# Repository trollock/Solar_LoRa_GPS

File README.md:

# Solar_LoRa_GPS
files related to the development of the Solar LoRa GPS radiotransceiver including information on the hardware and software

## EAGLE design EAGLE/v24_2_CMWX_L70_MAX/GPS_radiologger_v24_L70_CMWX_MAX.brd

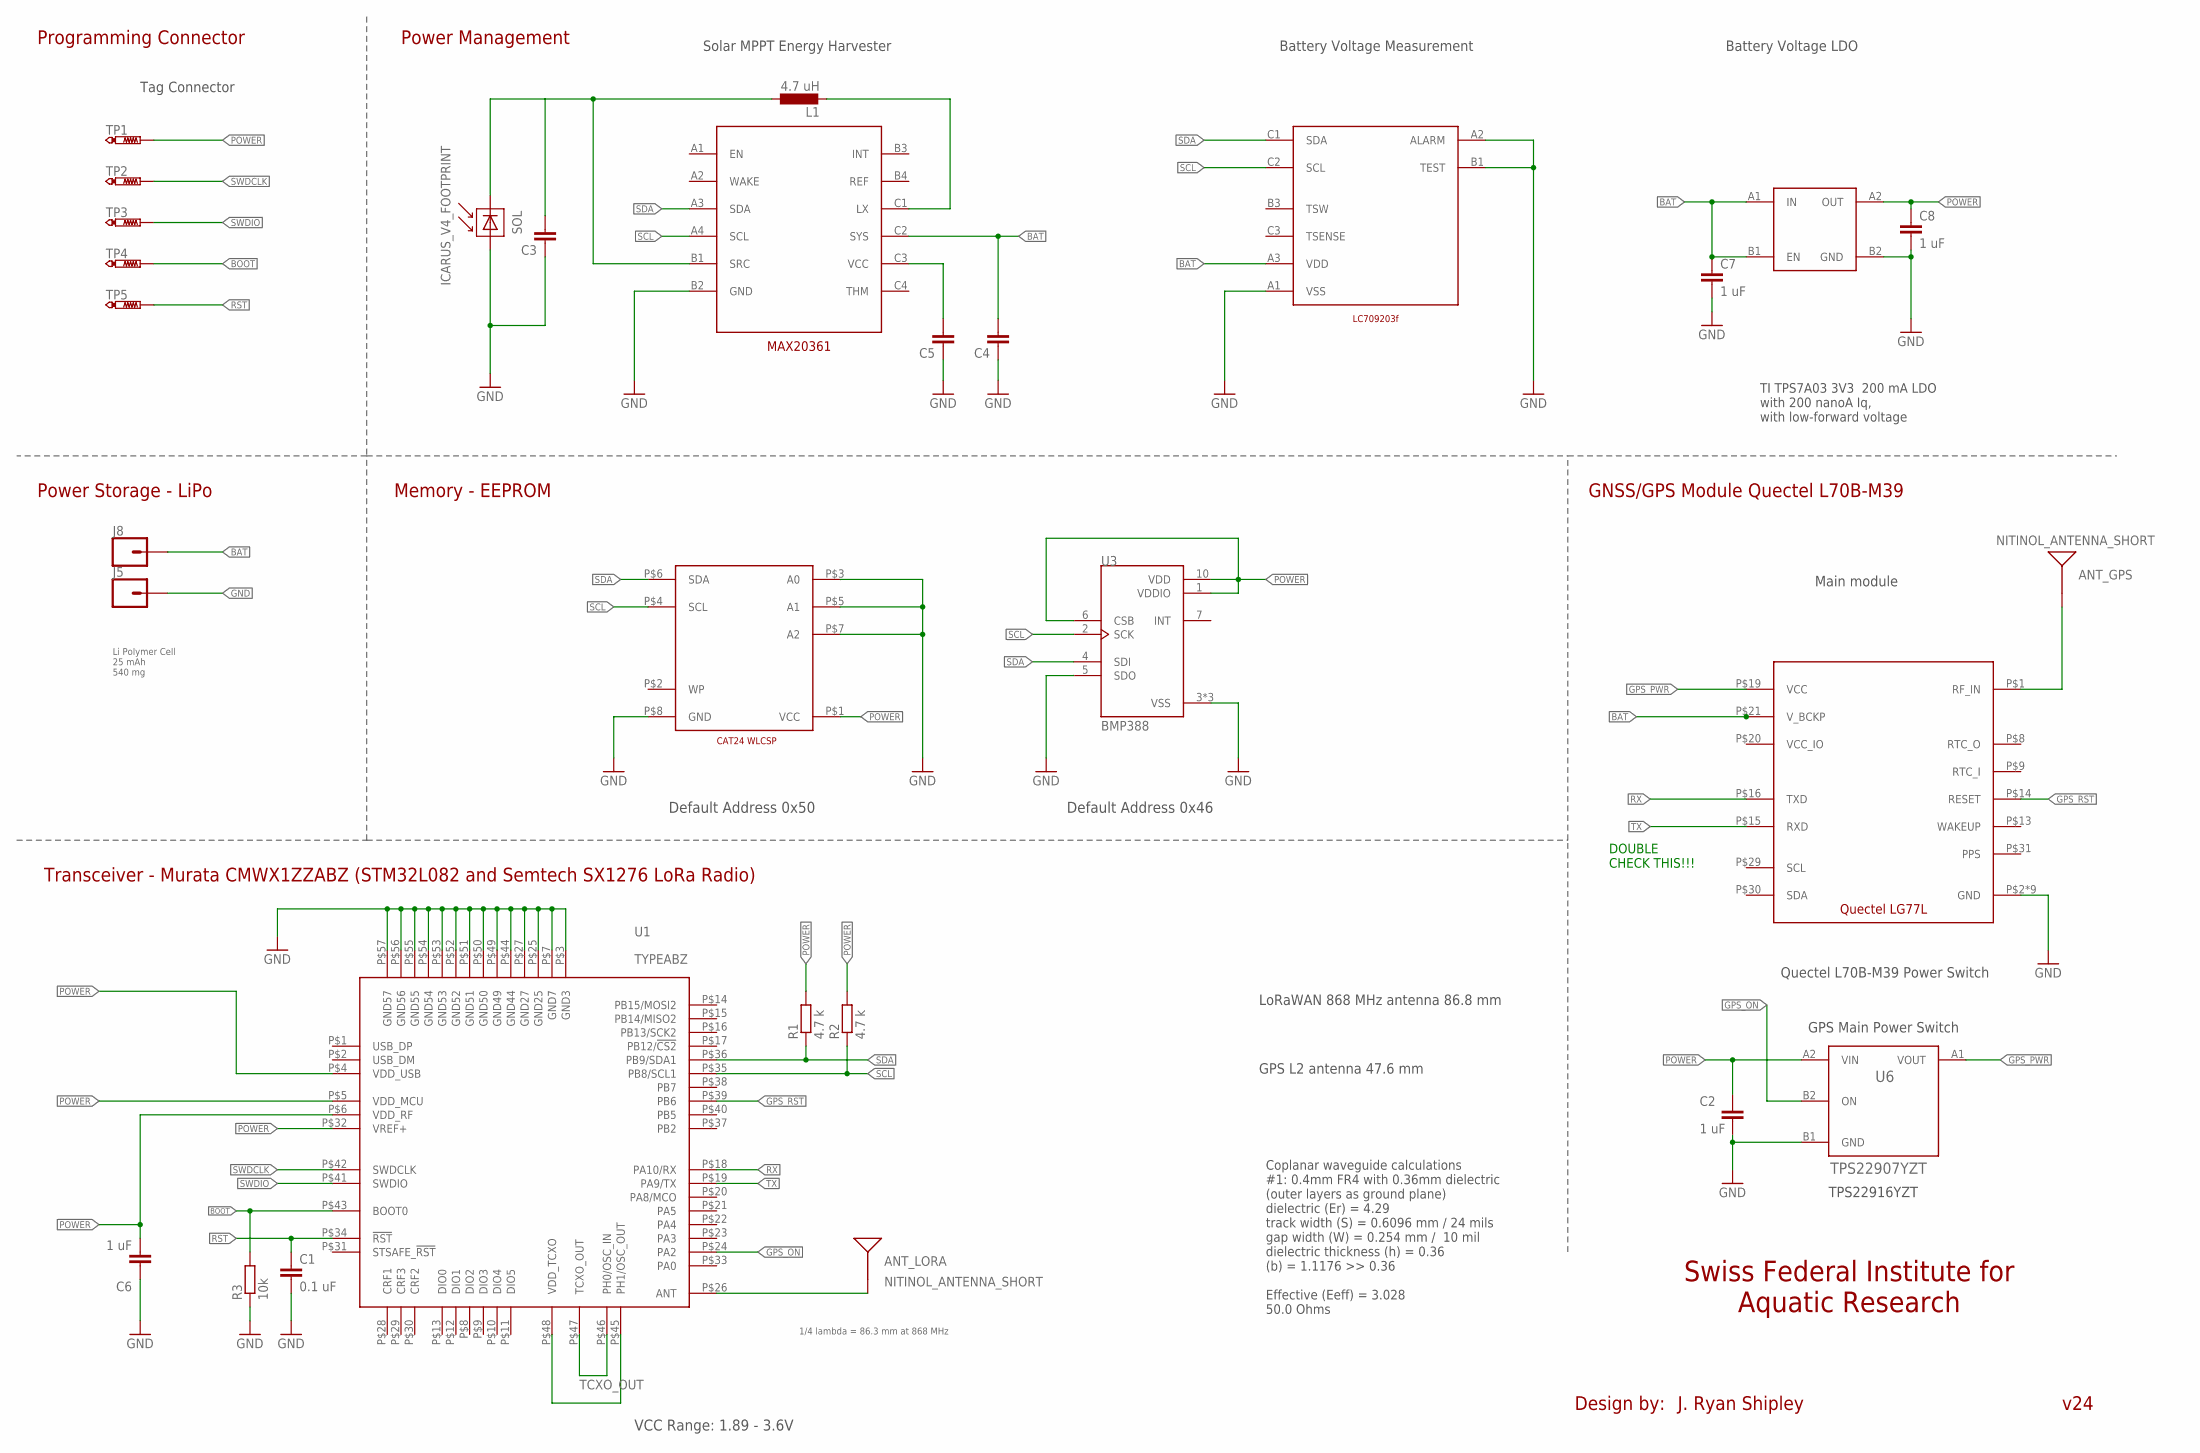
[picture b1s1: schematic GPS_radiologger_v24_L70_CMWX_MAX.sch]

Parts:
ANT_GPS: NITINOL_ANTENNA_SHORT; ICARUS_NITINOL_ANTENNA_SHORT
ANT_LORA: NITINOL_ANTENNA_SHORT; ICARUS_NITINOL_ANTENNA_SHORT
C1: 0.1 uF; C0201
C2, C6: 1 uF; C0201
C3: 10UF; 0603-TIGHT
C4, C5: 1.0UF; 0402-TIGHTER
C7, C8: 1 uF; 0402-CAP
J5, J8: CONN_01PTH_NO_SILK_SMALL; 1X01_SMALL
L1: 4.7 uH; INDC2016X120L
R1, R2: 4.7 k; R0201
R3: 10k; R0201
SOL: ICARUS_V4_FOOTPRINT; ICARUS_FULL_FOOTPRINT
TP1, TP2, TP3, TP4, TP5: PTR1TP08SQ; TP08SQ
U1: TYPEABZ
U3: BMP388; PQFN50P200X200X80-10N
U4: TPS7A03-DSBGA; BGA4N35P2X2_70X70X40N
U5: LC709203F; BGA9N50P3X3_160X175X50N
U6: TPS22907YZT; YFP0004-DSBGA
U7: CAT24_WLCSP8; WLCSP8
U8: MAX20361; BGA12N40P4X3_123X163X64N
U$1: LG77L

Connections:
BAT: C4.P$2 (2), C7.1, J8.P$1, U4.A1 (IN), U4.B1 (EN), U5.A3 (VDD), U8.C2 (SYS), U$1.P$21 (V_BCKP)
BOOT: R3.2, TP4.TP, U1.P$43 (BOOT0)
GND: C1.2, C2.2, C3.P$1 (1), C4.P$1 (1), C5.P$1 (1), C6.1, C7.2, C8.2, J5.P$1, R3.1, SOL.P$2 (MINUS), U1.P$3 (GND3), U1.P$7 (GND7), U1.P$25 (GND25), U1.P$27 (GND27), U1.P$44 (GND44), U1.P$49 (GND49), U1.P$50 (GND50), U1.P$51 (GND51), U1.P$52 (GND52), U1.P$53 (GND53), U1.P$54 (GND54), U1.P$55 (GND55), U1.P$56 (GND56), U1.P$57 (GND57), U3.3 (VSS), U3.5 (SDO), U3.8 (VSS), U3.9 (VSS), U4.B2 (GND), U5.A1 (VSS), U5.A2 (ALARM), U5.B1 (TEST), U6.B1 (GND), U7.P$3 (A0), U7.P$5 (A1), U7.P$7 (A2), U7.P$8 (GND), U8.B2 (GND), U$1.P$2 (GND), U$1.P$18 (GND), U$1.P$37 (GND), U$1.P$38 (GND), U$1.P$39 (GND), U$1.P$40 (GND), U$1.P$41 (GND), U$1.P$42 (GND), U$1.P$43 (GND)
GPS_ON: U1.P$24 (PA2), U6.B2 (ON)
GPS_PWR: U6.A1 (VOUT), U$1.P$19 (VCC)
GPS_RST: U1.P$39 (PB6), U$1.P$14 (RESET)
unnamed: U1.P$45 (PH1/OSC_OUT), U1.P$48 (VDD_TCXO)
unnamed: ANT_GPS.1, ANT_GPS.2, ANT_GPS.3, U$1.P$1 (RF_IN)
unnamed: L1.2, U8.C1 (LX)
unnamed: C5.P$2 (2), U8.C3 (VCC)
unnamed: ANT_LORA.1, ANT_LORA.2, ANT_LORA.3, U1.P$26 (ANT)
unnamed: C3.P$2 (2), L1.1, SOL.P$1 (PLUS), U8.B1 (SRC)
POWER: C2.1, C6.2, C8.1, R1.2, R2.2, TP1.TP, U1.P$4 (VDD_USB), U1.P$5 (VDD_MCU), U1.P$6 (VDD_RF), U1.P$32 (VREF+), U3.1 (VDDIO), U3.6 (CSB), U3.10 (VDD), U4.A2 (OUT), U6.A2 (VIN), U7.P$1 (VCC)
RST: C1.1, TP5.TP, U1.P$34 (!RST)
RX: U1.P$18 (PA10/RX), U$1.P$16 (TXD)
SCL: R2.1, U1.P$35 (PB8/SCL1), U3.2 (SCK), U5.C2 (SCL), U7.P$4 (SCL), U8.A4 (SCL)
SDA: R1.1, U1.P$36 (PB9/SDA1), U3.4 (SDI), U5.C1 (SDA), U7.P$6 (SDA), U8.A3 (SDA)
SWDCLK: TP2.TP, U1.P$42 (SWDCLK)
SWDIO: TP3.TP, U1.P$41 (SWDIO)
TCXO_OUT: U1.P$46 (PH0/OSC_IN), U1.P$47 (TCXO_OUT)
TX: U1.P$19 (PA9/TX), U$1.P$15 (RXD)

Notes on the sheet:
GNSS/GPS Module Quectel L70B-M39
VCC Range: 1.89 - 3.6V
Swiss Federal Institute for Aquatic Research
Transceiver - Murata CMWX1ZZABZ (STM32L082 and Semtech SX1276 LoRa Radio)
Programming Connector
Power Storage - LiPo
Design by:
J. Ryan Shipley
v24
Li Polymer Cell 25 mAh 540 mg
Power Management
Solar MPPT Energy Harvester
Memory - EEPROM
Main module
Coplanar waveguide calculations #1: 0.4mm FR4 with 0.36mm dielectric (outer layers as ground plane) dielectric (Er) = 4.29 track width (S) = 0.6096 mm / 24 mils gap width (W) = 0.254 mm / 10 mil dielectric thickness (h) = 0.36 (b) = 1.1176 >> 0.36 Effective (Eeff) = 3.028 50.0 Ohms
Tag Connector
Default Address 0x50
1/4 lambda = 86.3 mm at 868 MHz
GPS Main Power Switch
TI TPS7A03 3V3 200 mA LDO with 200 nanoA Iq, with low-forward voltage
Quectel L70B-M39 Power Switch
Battery Voltage Measurement
Battery Voltage LDO
Default Address 0x46
TPS22916YZT
GPS L2 antenna 47.6 mm
LoRaWAN 868 MHz antenna 86.8 mm
DOUBLE CHECK THIS!!!

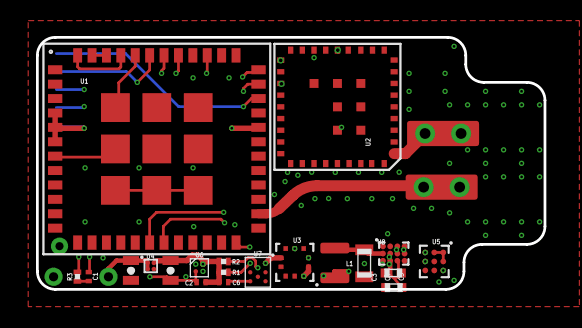
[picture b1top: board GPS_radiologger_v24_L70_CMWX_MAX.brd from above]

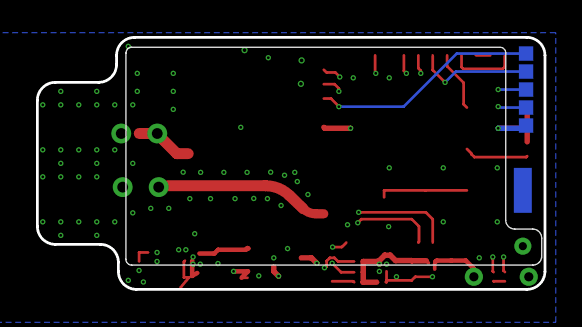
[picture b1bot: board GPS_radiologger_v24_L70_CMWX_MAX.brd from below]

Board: 4 copper layers, 28.2 x 14.0 mm, 30 parts (7 on the bottom side), 21 nets.

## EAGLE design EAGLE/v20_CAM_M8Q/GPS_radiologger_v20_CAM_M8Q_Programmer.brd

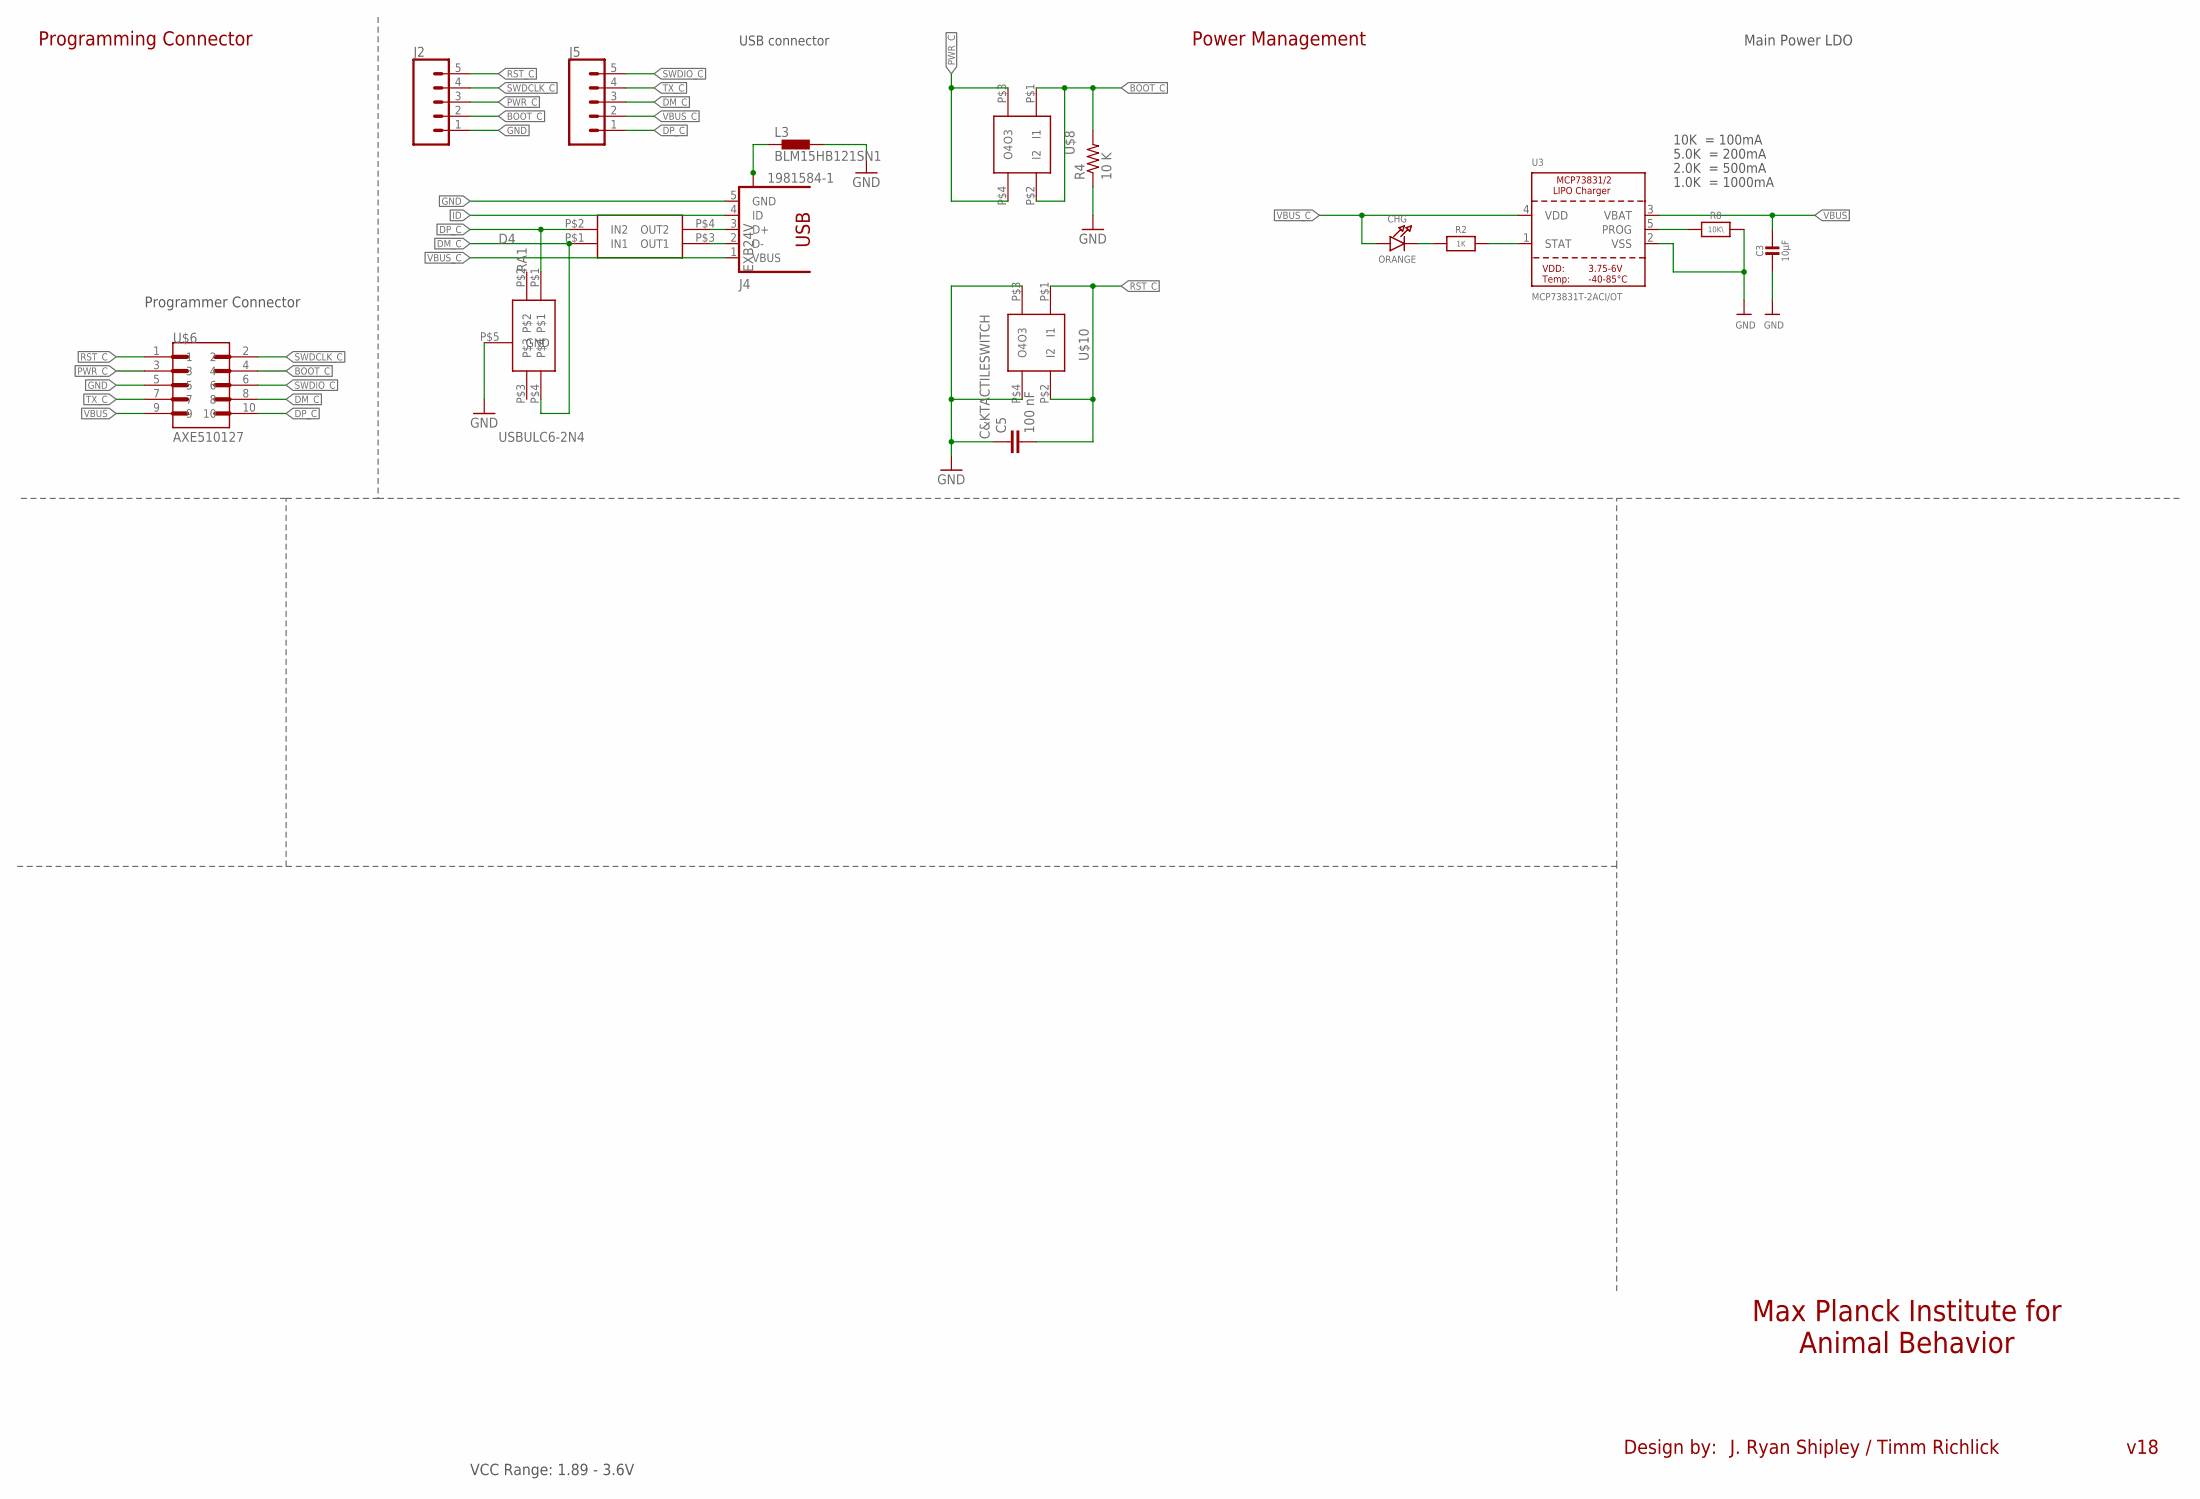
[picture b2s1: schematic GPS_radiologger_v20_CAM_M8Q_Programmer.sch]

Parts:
C3: 10µF; 0805-NO
C5: 100 nF; 0402-CAP
CHG: ORANGE; CHIPLED_0805_NOOUTLINE
D4: USBULC6-2N4
J2, J5: CONN_05; 1X05
J4: 1981584-1; MPN ZX62-AB-5PA(11)
L3: BLM15HB121SN1; 0402
R2: 1K; 0603-NO
R4: 10 K; 0402-RES
R8: 10K\; 0603-NO
RA1: EXB24V
U3: MCP73831T-2ACI/OT; SOT23-5
U$6: AXE510127
U$8, U$10: C&KTACTILESWITCH

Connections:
BOOT_C: J2.2, R4.2, U$6.4, U$8.P$1 (I1), U$8.P$2 (I2)
DM_C: D4.P$4, J5.3, RA1.P$1 (IN1), U$6.8
DP_C: D4.P$1, J5.1, RA1.P$2 (IN2), U$6.10
GND: C3.2, C5.1, D4.P$5 (GND), J2.1, J4.5 (GND), L3.2, R4.1, R8.2, U3.2 (VSS), U$6.5, U$10.P$3 (O3), U$10.P$4 (O4)
ID: J4.4 (ID)
unnamed: CHG.C, R2.1
unnamed: R2.2, U3.1 (STAT)
unnamed: R8.1, U3.5 (PROG)
unnamed: J4.3 (D+), RA1.P$4 (OUT2)
unnamed: J4.2 (D-), RA1.P$3 (OUT1)
PWR_C: J2.3, U$6.3, U$8.P$3 (O3), U$8.P$4 (O4)
RST_C: C5.2, J2.5, U$6.1, U$10.P$1 (I1), U$10.P$2 (I2)
SWDCLK_C: J2.4, U$6.2
SWDIO_C: J5.5, U$6.6
TX_C: J5.4, U$6.7
USB_SHIELD: J4.S1, J4.S2, J4.S3, J4.S4, L3.1
VBUS: C3.1, U3.3 (VBAT), U$6.9
VBUS_C: CHG.A, J4.1 (VBUS), J5.2, U3.4 (VDD)

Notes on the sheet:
VCC Range: 1.89 - 3.6V
Max Planck Institute for Animal Behavior
Programming Connector
Design by:
J. Ryan Shipley / Timm Richlick
v18
Power Management
Main Power LDO
USB connector
Programmer Connector
10K = 100mA
5.0K = 200mA
2.0K = 500mA
1.0K = 1000mA

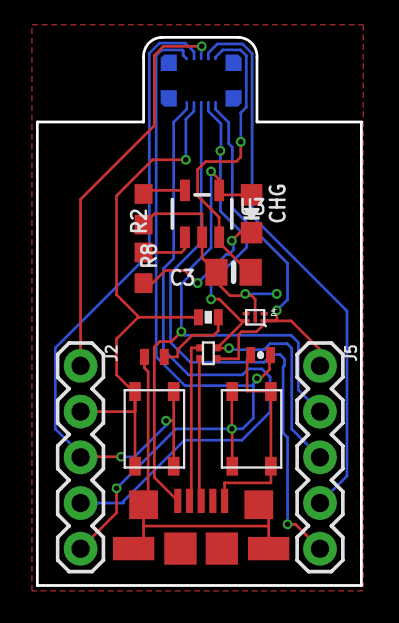
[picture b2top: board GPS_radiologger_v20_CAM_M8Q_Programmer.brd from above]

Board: 2 copper layers, 18.0 x 30.4 mm, 16 parts (1 on the bottom side), 17 nets.

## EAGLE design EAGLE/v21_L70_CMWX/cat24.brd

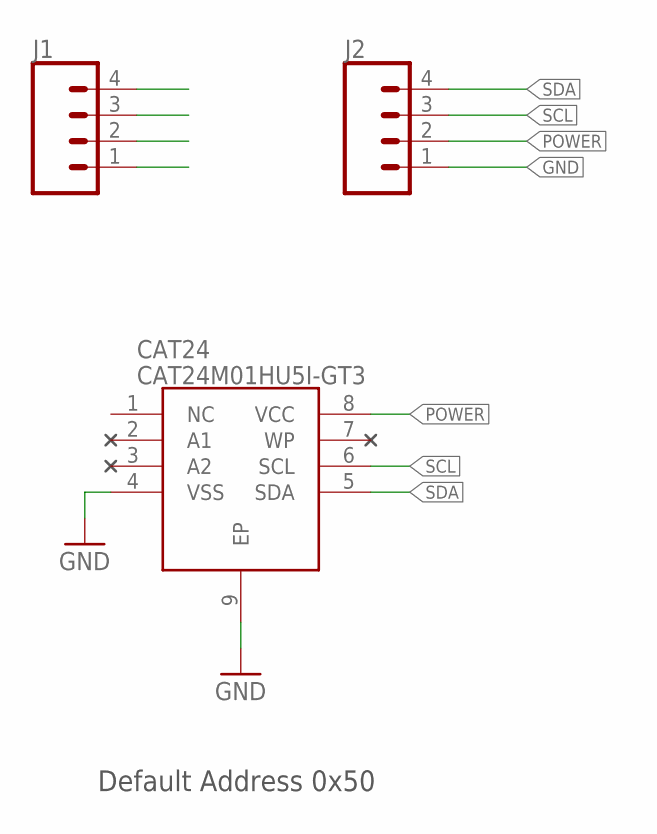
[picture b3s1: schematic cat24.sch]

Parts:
CAT24: CAT24M01HU5I-GT3; SON50P300X200X55-9N
J1, J2: CONN_041X04_NO_SILK; 1X04_NO_SILK

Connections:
GND: CAT24.4 (VSS), CAT24.9 (EP), J2.1
POWER: CAT24.8 (VCC), J2.2
SCL: CAT24.6 (SCL), J2.3
SDA: CAT24.5 (SDA), J2.4

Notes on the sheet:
Default Address 0x50

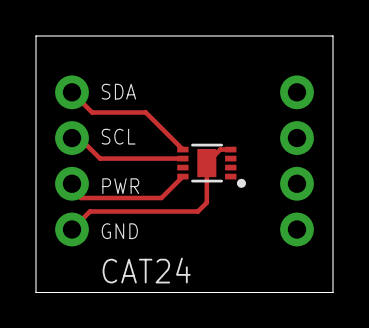
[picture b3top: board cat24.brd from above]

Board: 2 copper layers, 16.5 x 14.2 mm, 3 parts (0 on the bottom side), 4 nets.

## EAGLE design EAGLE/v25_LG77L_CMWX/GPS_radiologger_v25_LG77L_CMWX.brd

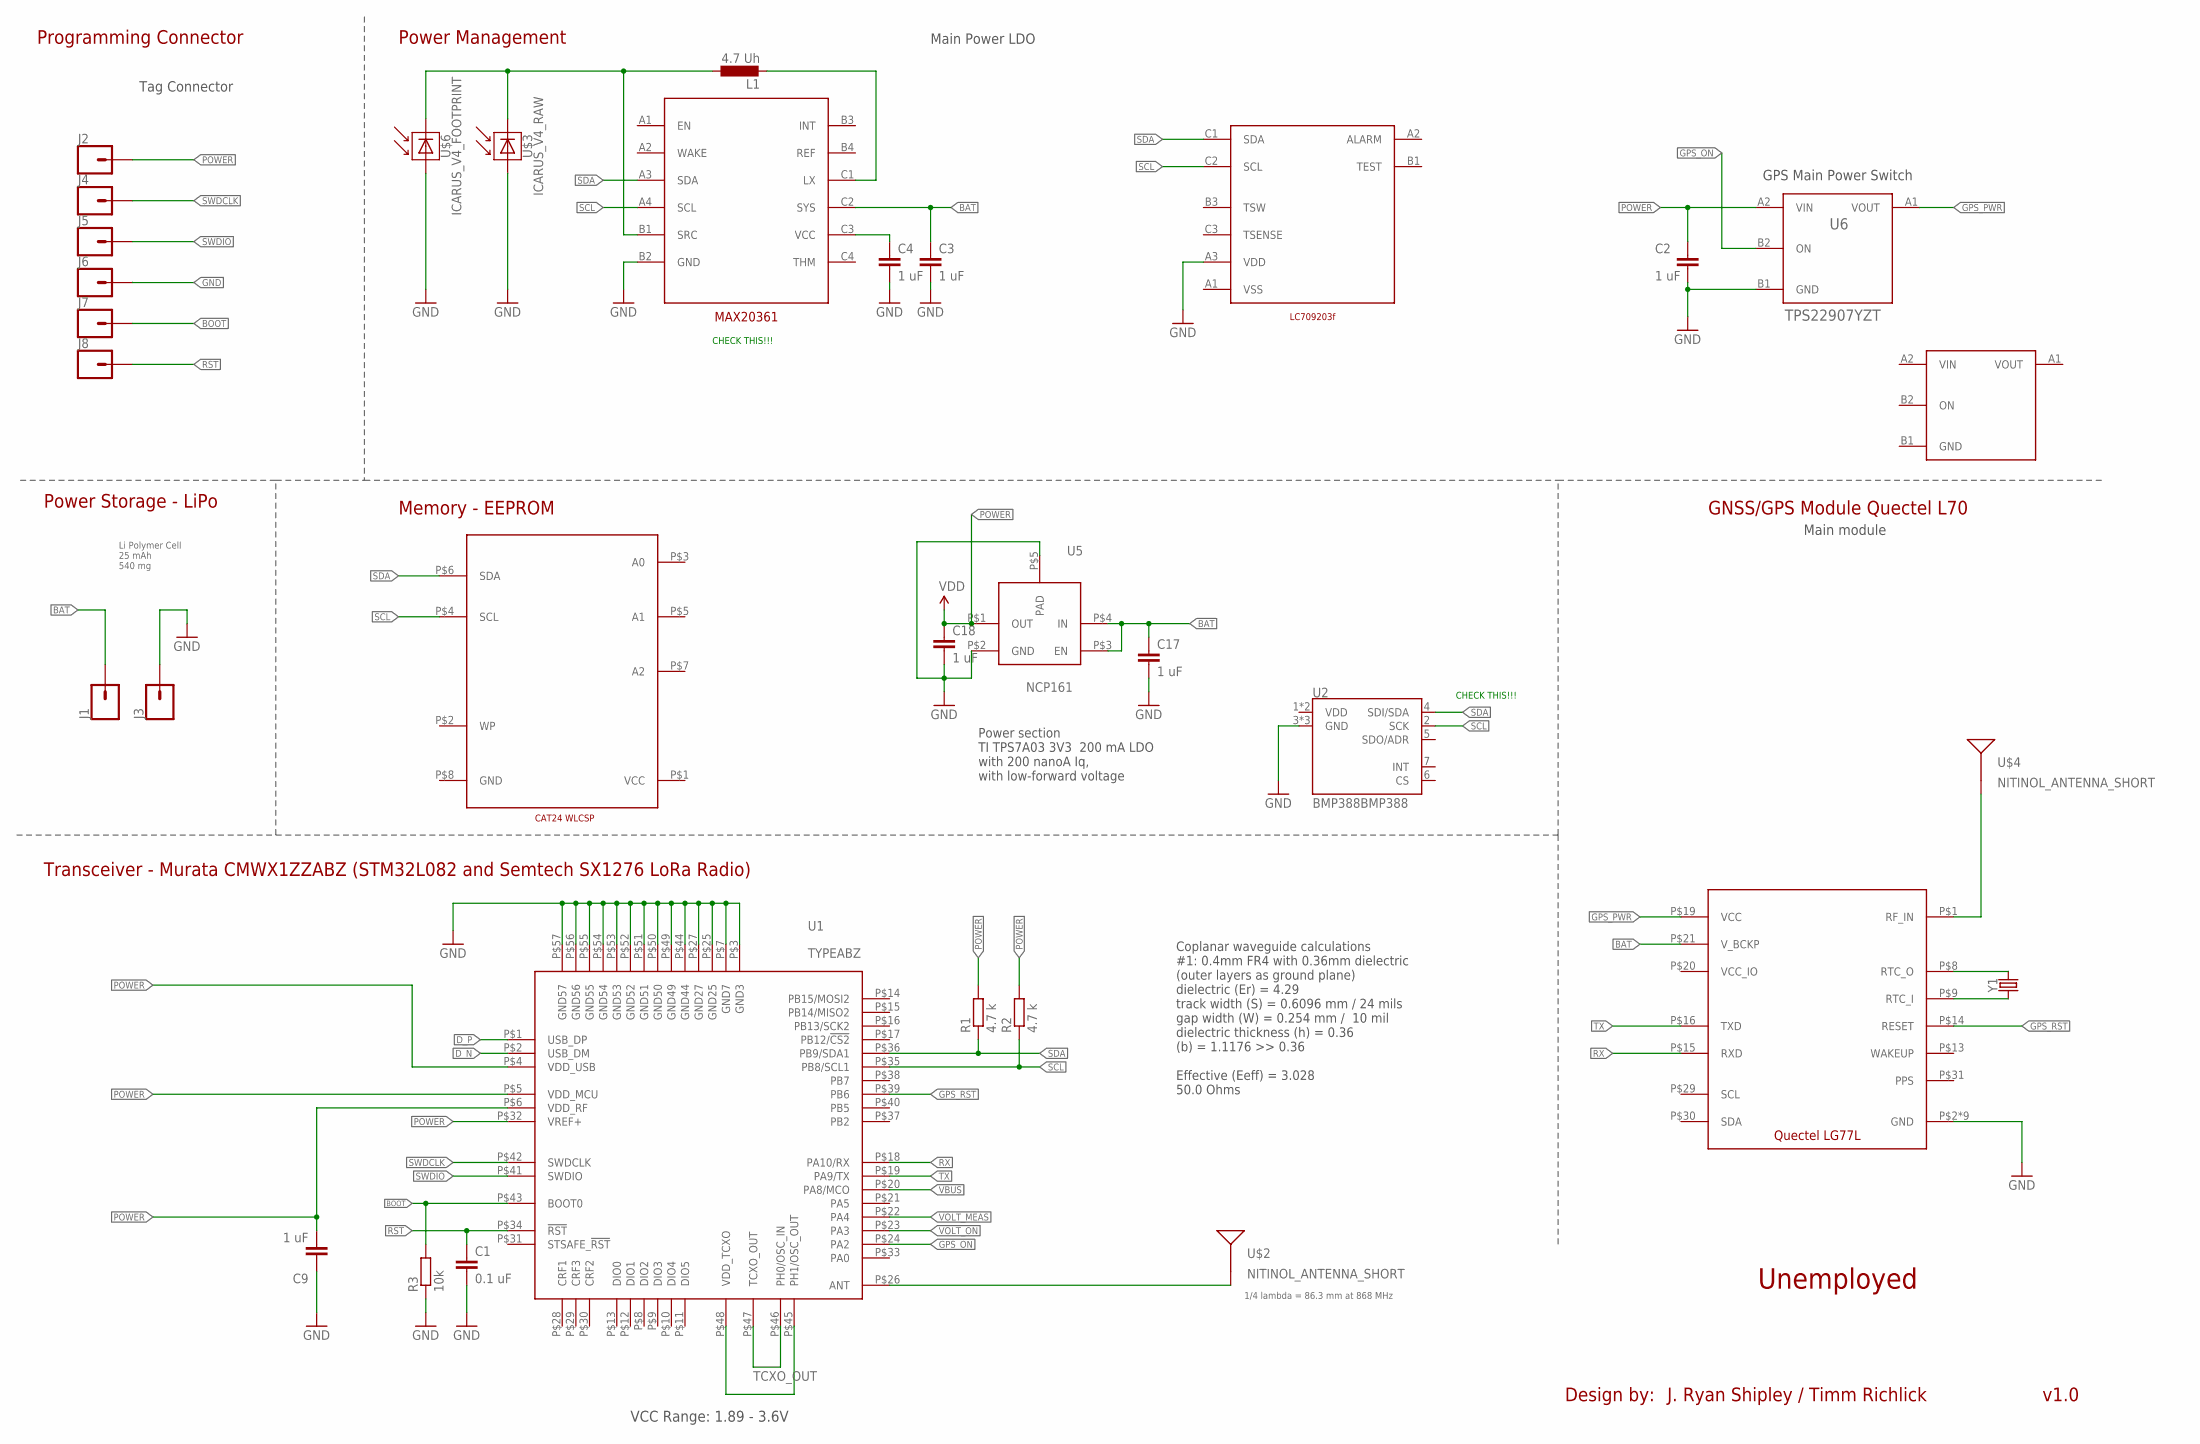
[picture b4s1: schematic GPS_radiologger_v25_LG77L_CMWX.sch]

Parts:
C1: 0.1 uF; C0201
C2, C3, C4, C9: 1 uF; C0201
C17, C18: 1 uF; 0402-CAP
J1, J2, J3, J4, J5, J6, J7, J8: CONN_01PTH_NO_SILK_SMALL; 1X01_SMALL
L1: 4.7 Uh; L2012C
R1, R2: 4.7 k; R0201
R3: 10k; R0201
U1: TYPEABZ
U2: BMP388BMP388; LGA-10(2X2)
U5: NCP161
U6: TPS22907YZT; YFP0004-DSBGA
U$1: MAX20361; BGA12N40P4X3_123X163X64N
U$2, U$4: NITINOL_ANTENNA_SHORT; ICARUS_NITINOL_ANTENNA_SHORT
U$3: ICARUS_V4_RAW; ICARUS_FULL_TOP
U$5: CAT24_WLCSP8; WLCSP8
U$6: ICARUS_V4_FOOTPRINT; ICARUS_FULL_FOOTPRINT
U$7: LG77L
U$8: LC709203F; BGA9N50P3X3_160X175X50N
U$9: TPS22916CL; YFP0004-DSBGA
Y1: CRYSTAL-32.768KHZ; CRYSTAL-SMD-1.0X1.2MM

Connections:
BAT: C3.1, C17.1, J1.P$1, U5.P$3 (EN), U5.P$4 (IN), U$1.C2 (SYS), U$7.P$21 (V_BCKP)
BOOT: J7.P$1, R3.2, U1.P$43 (BOOT0)
D_N: U1.P$2 (USB_DM)
D_P: U1.P$1 (USB_DP)
GND: C1.2, C2.2, C3.2, C4.2, C9.1, C17.2, C18.2, J3.P$1, J6.P$1, R3.1, U1.P$3 (GND3), U1.P$7 (GND7), U1.P$25 (GND25), U1.P$27 (GND27), U1.P$44 (GND44), U1.P$49 (GND49), U1.P$50 (GND50), U1.P$51 (GND51), U1.P$52 (GND52), U1.P$53 (GND53), U1.P$54 (GND54), U1.P$55 (GND55), U1.P$56 (GND56), U1.P$57 (GND57), U2.3 (GND), U2.8 (GND), U2.9 (GND), U5.P$2 (GND), U5.P$5 (PAD), U6.B1 (GND), U$1.B2 (GND), U$3.P$2 (MINUS), U$6.P$2 (MINUS), U$7.P$2 (GND), U$7.P$18 (GND), U$7.P$37 (GND), U$7.P$38 (GND), U$7.P$39 (GND), U$7.P$40 (GND), U$7.P$41 (GND), U$7.P$42 (GND), U$7.P$43 (GND), U$8.A3 (VDD)
GPS_ON: U1.P$24 (PA2), U6.B2 (ON)
GPS_PWR: U6.A1 (VOUT), U$7.P$19 (VCC)
GPS_RST: U1.P$39 (PB6), U$7.P$14 (RESET)
unnamed: U1.P$45 (PH1/OSC_OUT), U1.P$48 (VDD_TCXO)
unnamed: U$4.1, U$4.2, U$4.3, U$7.P$1 (RF_IN)
unnamed: U$7.P$8 (RTC_O), Y1.P$2 (2)
unnamed: U$7.P$9 (RTC_I), Y1.P$1 (1)
unnamed: L1.2, U$1.C1 (LX)
unnamed: C4.1, U$1.C3 (VCC)
unnamed: U1.P$26 (ANT), U$2.1, U$2.2, U$2.3
POWER: C2.1, C9.2, C18.1, J2.P$1, R1.2, R2.2, U1.P$4 (VDD_USB), U1.P$5 (VDD_MCU), U1.P$6 (VDD_RF), U1.P$32 (VREF+), U5.P$1 (OUT), U6.A2 (VIN)
RST: C1.1, J8.P$1, U1.P$34 (!RST)
RX: U1.P$18 (PA10/RX), U$7.P$15 (RXD)
SCL: R2.1, U1.P$35 (PB8/SCL1), U2.2 (SCK), U$1.A4 (SCL), U$5.P$4 (SCL), U$8.C2 (SCL)
SDA: R1.1, U1.P$36 (PB9/SDA1), U2.4 (SDI/SDA), U$1.A3 (SDA), U$5.P$6 (SDA), U$8.C1 (SDA)
SOL_IN: L1.1, U$1.B1 (SRC), U$3.P$1 (PLUS), U$6.P$1 (PLUS)
SWDCLK: J4.P$1, U1.P$42 (SWDCLK)
SWDIO: J5.P$1, U1.P$41 (SWDIO)
TCXO_OUT: U1.P$46 (PH0/OSC_IN), U1.P$47 (TCXO_OUT)
TX: U1.P$19 (PA9/TX), U$7.P$16 (TXD)
VBUS: U1.P$20 (PA8/MCO)
VOLT_MEAS: U1.P$22 (PA4)
VOLT_ON: U1.P$23 (PA3)

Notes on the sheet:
GNSS/GPS Module Quectel L70
VCC Range: 1.89 - 3.6V
Unemployed
Transceiver - Murata CMWX1ZZABZ (STM32L082 and Semtech SX1276 LoRa Radio)
Programming Connector
Power Storage - LiPo
Design by:
J. Ryan Shipley / Timm Richlick
v1.0
Li Polymer Cell 25 mAh 540 mg
Power Management
Main Power LDO
Memory - EEPROM
Main module
Coplanar waveguide calculations #1: 0.4mm FR4 with 0.36mm dielectric (outer layers as ground plane) dielectric (Er) = 4.29 track width (S) = 0.6096 mm / 24 mils gap width (W) = 0.254 mm / 10 mil dielectric thickness (h) = 0.36 (b) = 1.1176 >> 0.36 Effective (Eeff) = 3.028 50.0 Ohms
Tag Connector
1/4 lambda = 86.3 mm at 868 MHz
GPS Main Power Switch
Power section TI TPS7A03 3V3 200 mA LDO with 200 nanoA Iq, with low-forward voltage
CHECK THIS!!!

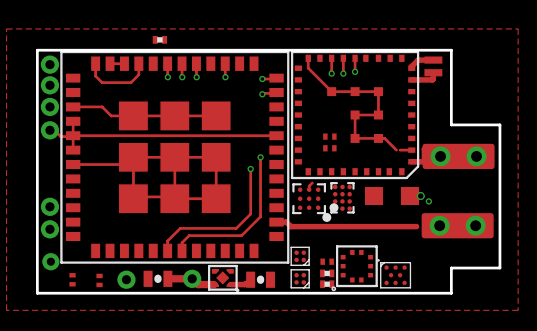
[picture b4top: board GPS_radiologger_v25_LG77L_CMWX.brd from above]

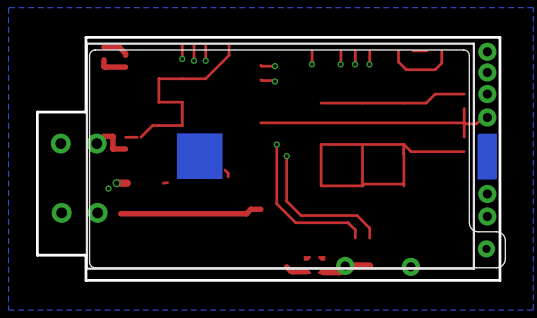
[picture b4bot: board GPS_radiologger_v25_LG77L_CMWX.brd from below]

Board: 4 copper layers, 25.7 x 13.5 mm, 33 parts (3 on the bottom side), 23 nets.

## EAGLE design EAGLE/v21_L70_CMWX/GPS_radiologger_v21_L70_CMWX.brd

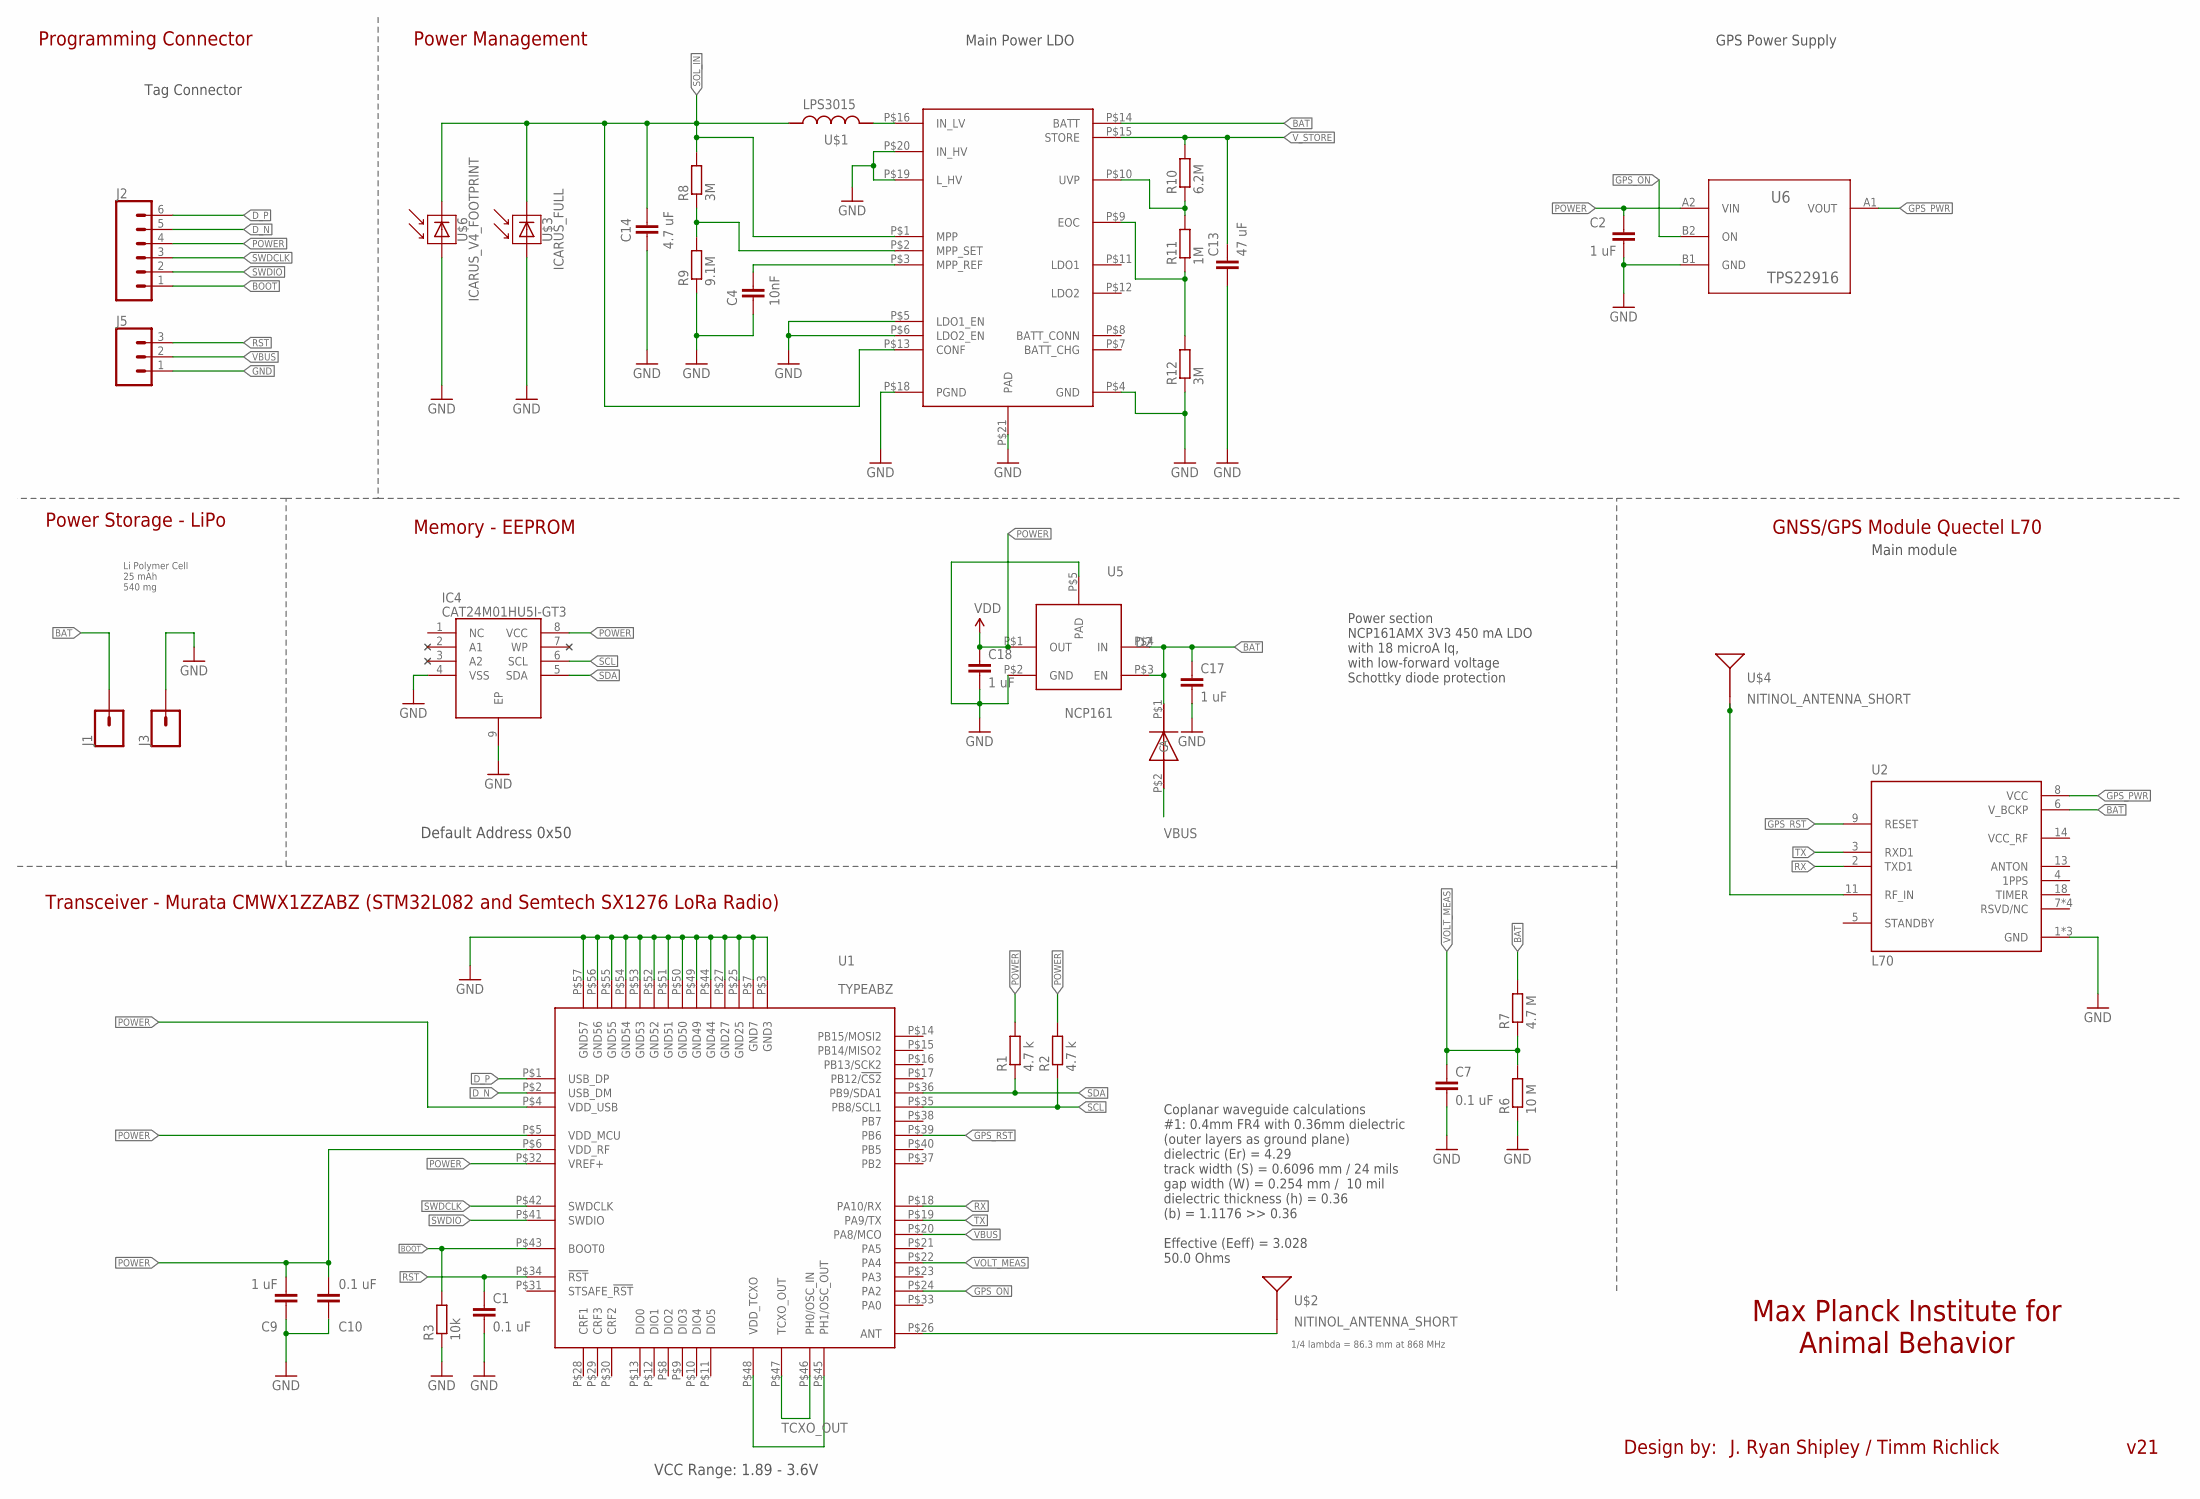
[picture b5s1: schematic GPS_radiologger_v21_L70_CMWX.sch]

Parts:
C1, C7, C10: 0.1 uF; C0201
C2, C9: 1 uF; C0201
C4: 10nF; C0201
C13: 47 uF; C0603
C14: 4.7 uF; C0201
C17, C18: 1 uF; 0402-CAP
D2: CDSQR4148-HF
IC4: CAT24M01HU5I-GT3; SON50P300X200X55-9N
J1, J3: CONN_01PTH_NO_SILK_SMALL; 1X01_SMALL
J2: CONN_061.27MM; 1X06_1.27MM
J5: CONN_031X03_1.27_NO_SILK; 1X03_1.27MM_NO_SILK
R1, R2: 4.7 k; R0201
R3: 10k; R0201
R6: 10 M; R0201
R7: 4.7 M; R0201
R8, R12: 3M; R0201
R9: 9.1M; R0201
R10: 6.2M; R0201
R11: 1M; R0201
U1: TYPEABZ
U2: L70; XCVR_L70
U4: SPV1050
U5: NCP161
U6: TPS22916
U$1: LPS3015; LPS_3015
U$2, U$4: NITINOL_ANTENNA_SHORT; ICARUS_NITINOL_ANTENNA_SHORT
U$3: ICARUS_FULL
U$6: ICARUS_V4_FOOTPRINT; ICARUS_FULL_FOOTPRINT

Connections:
BAT: C17.1, D2.P$1 (C), J1.P$1, R7.2, U2.6 (V_BCKP), U4.P$14 (BATT), U5.P$3 (EN), U5.P$4 (IN)
BOOT: J2.1, R3.2, U1.P$43 (BOOT0)
D_N: J2.5, U1.P$2 (USB_DM)
D_P: J2.6, U1.P$1 (USB_DP)
GND: C1.2, C2.2, C4.2, C7.2, C9.1, C10.1, C13.2, C14.2, C17.2, C18.2, IC4.4 (VSS), IC4.9 (EP), J3.P$1, J5.1, R3.1, R6.1, R9.1, R12.1, U1.P$3 (GND3), U1.P$7 (GND7), U1.P$25 (GND25), U1.P$27 (GND27), U1.P$44 (GND44), U1.P$49 (GND49), U1.P$50 (GND50), U1.P$51 (GND51), U1.P$52 (GND52), U1.P$53 (GND53), U1.P$54 (GND54), U1.P$55 (GND55), U1.P$56 (GND56), U1.P$57 (GND57), U2.1 (GND), U2.10 (GND), U2.12 (GND), U4.P$4 (GND), U4.P$5 (LDO1_EN), U4.P$6 (LDO2_EN), U4.P$18 (PGND), U4.P$19 (L_HV), U4.P$20 (IN_HV), U4.P$21 (PAD), U5.P$2 (GND), U5.P$5 (PAD), U6.B1 (GND), U$3.P$2 (MINUS), U$6.P$3 (MINUS)
GPS_ON: U1.P$24 (PA2), U6.B2 (ON)
GPS_PWR: U2.8 (VCC), U6.A1 (VOUT)
GPS_RST: U1.P$39 (PB6), U2.9 (RESET)
unnamed: U1.P$45 (PH1/OSC_OUT), U1.P$48 (VDD_TCXO)
unnamed: U2.11 (RF_IN), U$4.1, U$4.2, U$4.3
unnamed: U4.P$16 (IN_LV), U$1.P$2 (2)
unnamed: R8.1, R9.2, U4.P$2 (MPP_SET)
unnamed: R10.1, R11.2, U4.P$10 (UVP)
unnamed: R11.1, R12.2, U4.P$9 (EOC)
unnamed: U1.P$26 (ANT), U$2.1, U$2.2, U$2.3
unnamed: C4.1, U4.P$3 (MPP_REF)
POWER: C2.1, C9.2, C10.2, C18.1, IC4.8 (VCC), J2.4, R1.2, R2.2, U1.P$4 (VDD_USB), U1.P$5 (VDD_MCU), U1.P$6 (VDD_RF), U1.P$32 (VREF+), U5.P$1 (OUT), U6.A2 (VIN)
RST: C1.1, J5.3, U1.P$34 (!RST)
RX: U1.P$18 (PA10/RX), U2.2 (TXD1)
SCL: IC4.6 (SCL), R2.1, U1.P$35 (PB8/SCL1)
SDA: IC4.5 (SDA), R1.1, U1.P$36 (PB9/SDA1)
SOL_IN: C14.1, R8.2, U4.P$1 (MPP), U4.P$13 (CONF), U$1.P$1 (1), U$3.P$1 (PLUS), U$6.P$1 (PLUS)
SWDCLK: J2.3, U1.P$42 (SWDCLK)
SWDIO: J2.2, U1.P$41 (SWDIO)
TCXO_OUT: U1.P$46 (PH0/OSC_IN), U1.P$47 (TCXO_OUT)
TX: U1.P$19 (PA9/TX), U2.3 (RXD1)
VBUS: D2.P$2 (A), J5.2, U1.P$20 (PA8/MCO)
VOLT_MEAS: C7.1, R6.2, R7.1, U1.P$22 (PA4)
V_STORE: C13.1, R10.2, U4.P$15 (STORE)

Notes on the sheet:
GNSS/GPS Module Quectel L70
VCC Range: 1.89 - 3.6V
Max Planck Institute for Animal Behavior
Transceiver - Murata CMWX1ZZABZ (STM32L082 and Semtech SX1276 LoRa Radio)
Programming Connector
Power Storage - LiPo
Design by:
J. Ryan Shipley / Timm Richlick
v21
Li Polymer Cell 25 mAh 540 mg
Power Management
Main Power LDO
Memory - EEPROM
Main module
Coplanar waveguide calculations #1: 0.4mm FR4 with 0.36mm dielectric (outer layers as ground plane) dielectric (Er) = 4.29 track width (S) = 0.6096 mm / 24 mils gap width (W) = 0.254 mm / 10 mil dielectric thickness (h) = 0.36 (b) = 1.1176 >> 0.36 Effective (Eeff) = 3.028 50.0 Ohms
Tag Connector
Default Address 0x50
1/4 lambda = 86.3 mm at 868 MHz
GPS Power Supply
Power section NCP161AMX 3V3 450 mA LDO with 18 microA Iq, with low-forward voltage Schottky diode protection

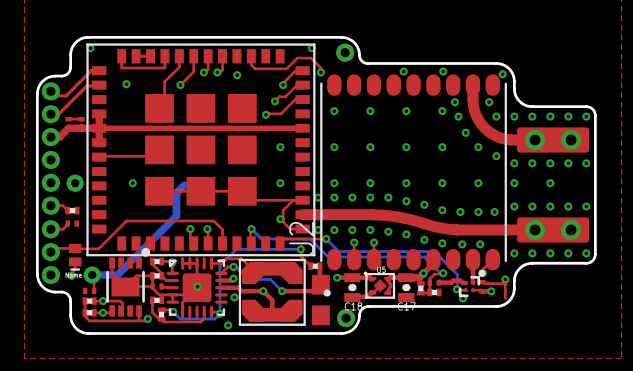
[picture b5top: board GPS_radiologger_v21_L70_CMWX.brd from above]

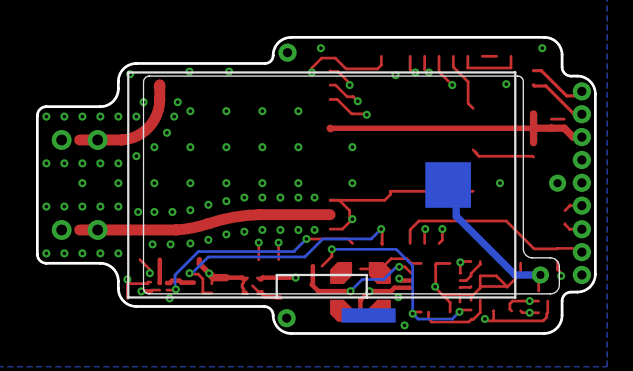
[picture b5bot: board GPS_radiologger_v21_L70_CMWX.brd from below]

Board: 4 copper layers, 31.0 x 16.4 mm, 36 parts (2 on the bottom side), 29 nets.

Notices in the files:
parts and their libraries:
SparkFun-Connectors: Licensing: Creative Commons ShareAlike 4.0 International - https://creativecommons.org/licenses/by-sa/4.0
con-usb: Copyright (C) 2008, Bob Starr
